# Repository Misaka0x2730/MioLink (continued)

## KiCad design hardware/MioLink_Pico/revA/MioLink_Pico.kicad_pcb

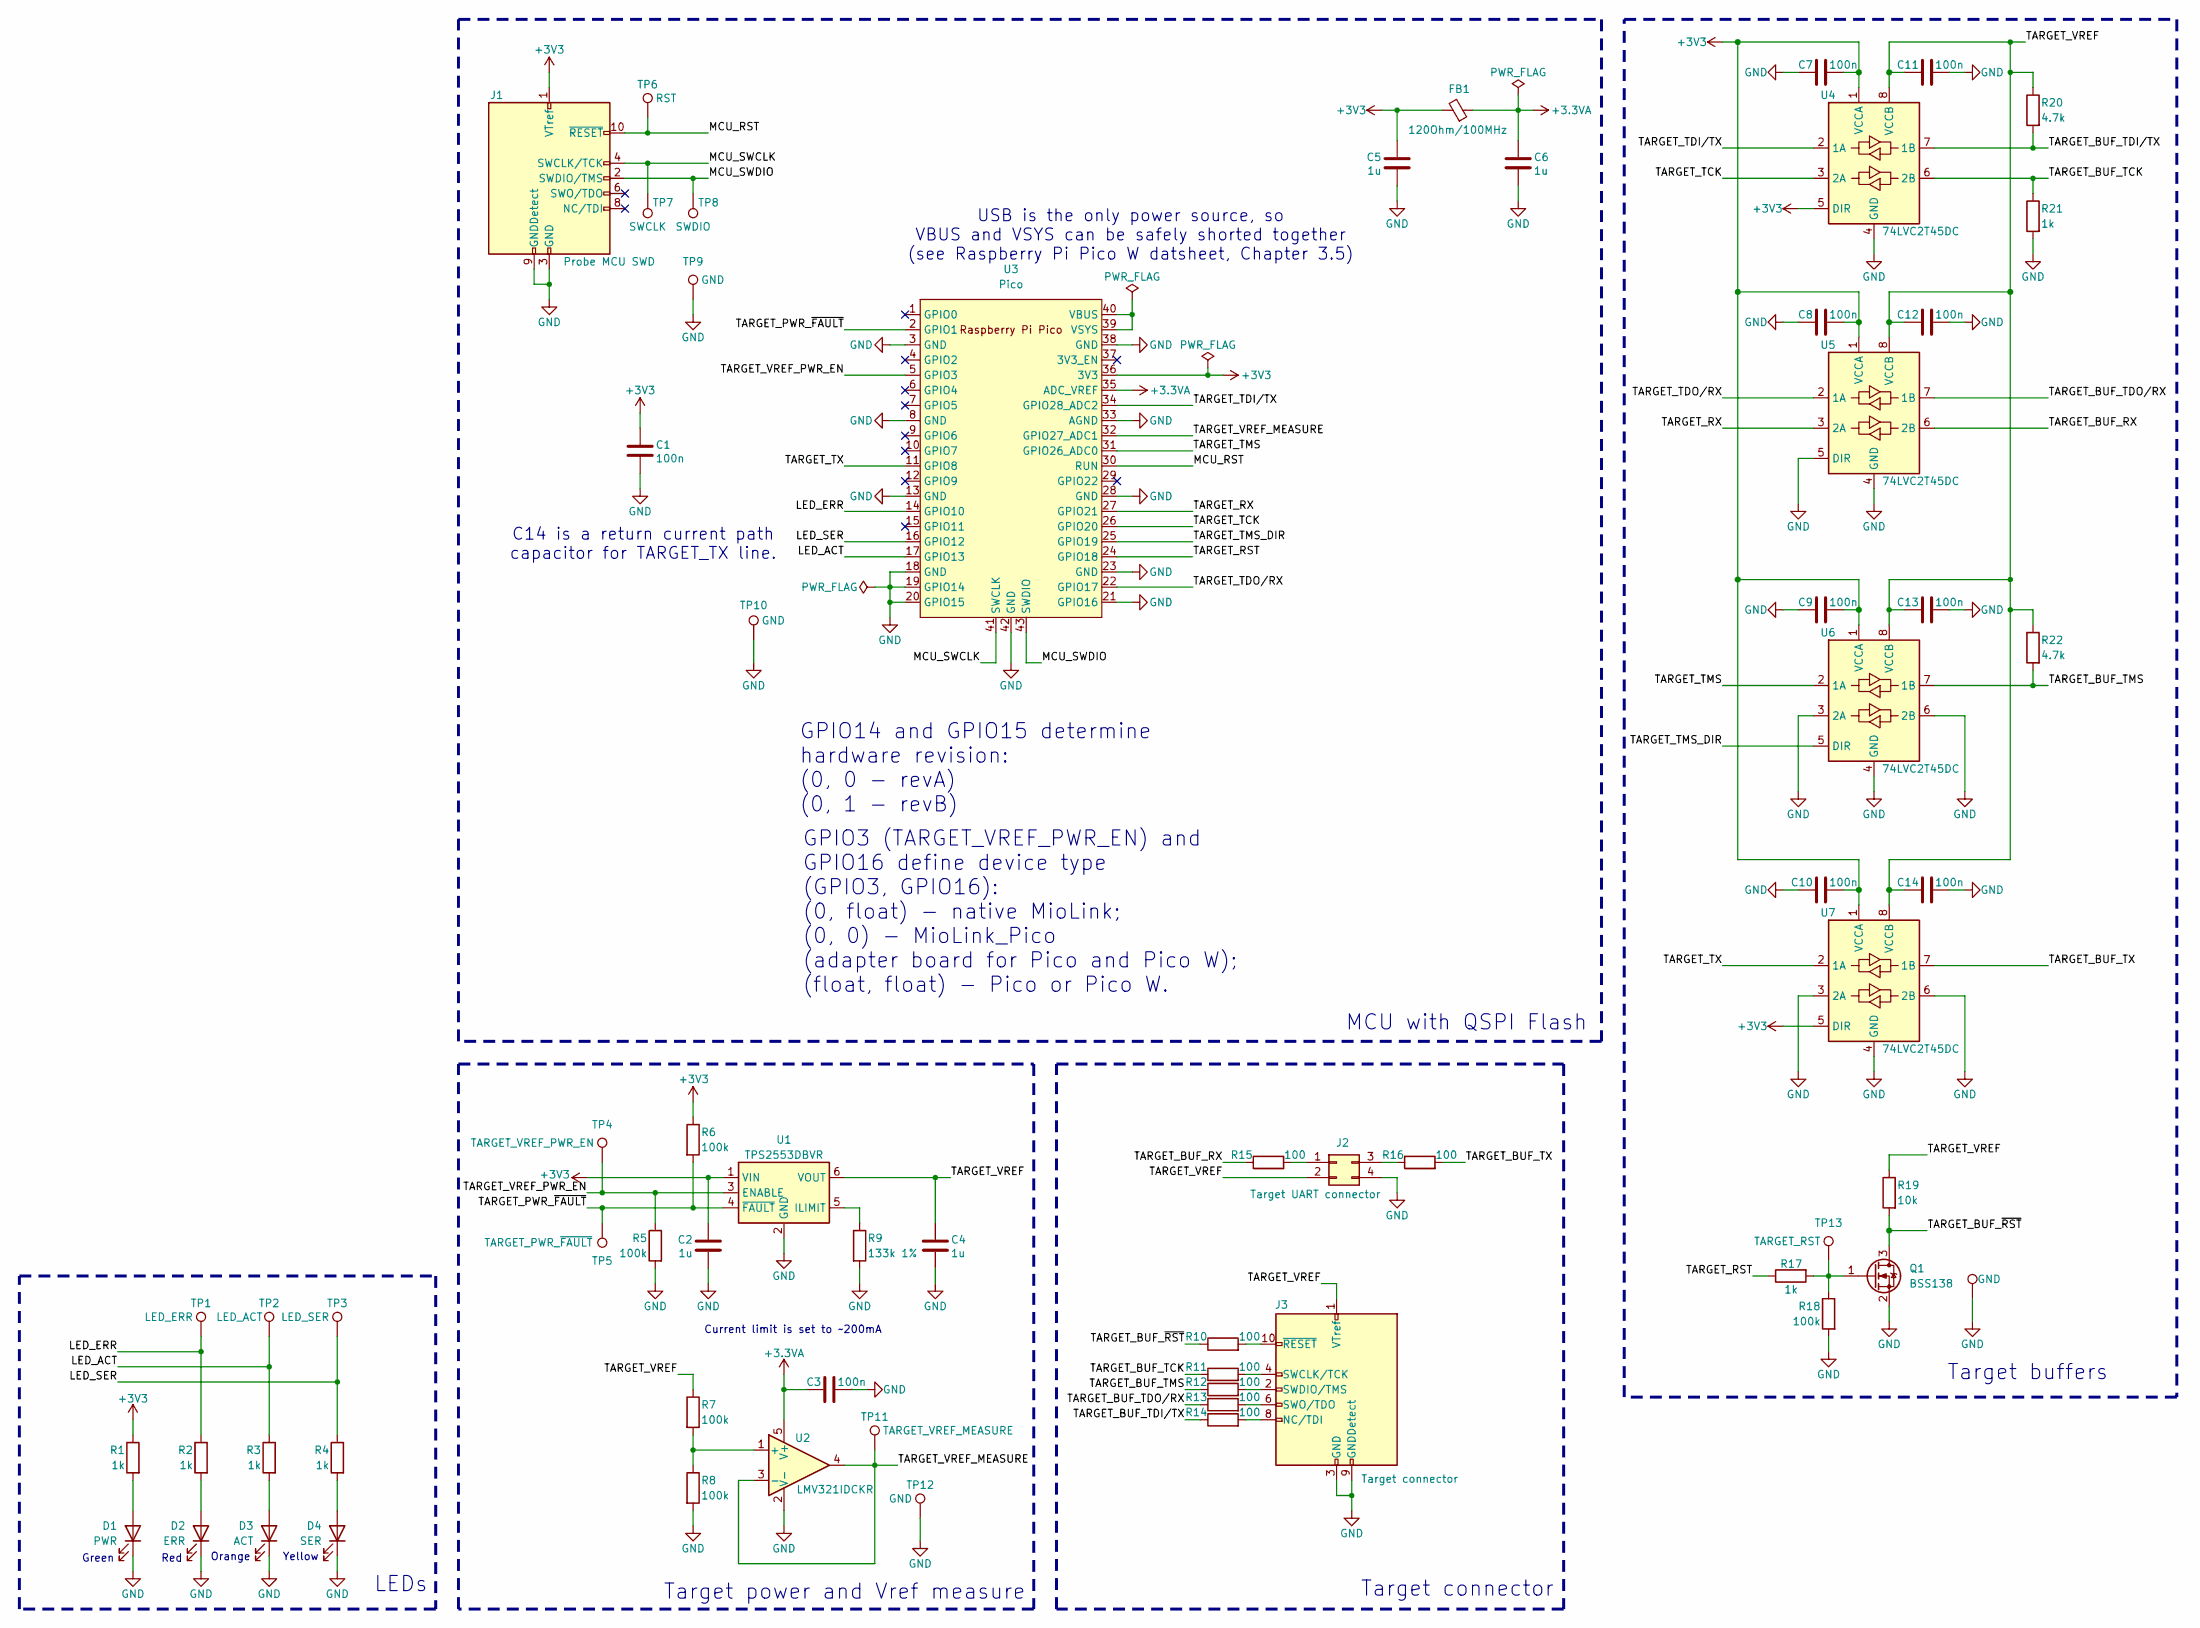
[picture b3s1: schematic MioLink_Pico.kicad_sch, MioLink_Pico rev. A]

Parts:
C1, C3, C7, C8, C9, C10, C11, C12, C13, C14: 100n; C_0402_1005Metric; Part Number CL05B104KO5NNNC; LCSC C1525
C2, C4, C5, C6: 1u; C_0402_1005Metric; Part Number CL05A105KA5NQNC; LCSC C52923
D1: PWR; LED_1206_3216Metric; Part Number XL-3216SYGC; LCSC C965826
D2: ERR; LED_1206_3216Metric; Part Number XL-3216SURC; LCSC C965822
D3: ACT; LED_1206_3216Metric; Part Number XL-3216UOC; LCSC C965823
D4: SER; LED_1206_3216Metric; Part Number XL-3216UYC; LCSC C965824
FB1: 120Ohm/100MHz; L_0603_1608Metric; Part Number BLM18PG121SN1D; LCSC C14709
J1: Probe MCU SWD; PinHeader_2x05_P1.27mm_Vertical_SMD; Part Number 20021121-00010T4LF; LCSC C598540
J2: Target UART connector; PinHeader_2x02_P2.54mm_Horizontal; Part Number PZ254-2-02-W-8.5; LCSC C2894982
J3: Target connector; IDC-Header_2x05_P2.54mm_Horizontal; Part Number 0502A001A1BC; LCSC C7434504
Q1: BSS138; SOT-23; Part Number BSS138LT1G; LCSC C82045
R1, R2, R3, R4, R17, R21: 1k; R_0402_1005Metric; Part Number 0402WGF1001TCE; LCSC C11702
R5, R6, R7, R8, R18: 100k; R_0402_1005Metric; Part Number 0402WGF1003TCE; LCSC C25741
R9: 133k 1%; R_0402_1005Metric; Part Number 0402WGF1333TCE; LCSC C25753
R10, R11, R12, R13, R14, R15, R16: 100; R_0402_1005Metric; Part Number 0402WGF1000TCE; LCSC C25076
R19: 10k; R_0402_1005Metric; Part Number 0402WGF1002TCE; LCSC C25744
R20, R22: 4.7k; R_0402_1005Metric; Part Number 0402WGF4701TCE; LCSC C25900
TP1: LED_ERR; TestPoint_Pad_D1.0mm
TP2: LED_ACT; TestPoint_Pad_D1.0mm
TP3: LED_SER; TestPoint_Pad_D1.0mm
TP4: TARGET_VREF_PWR_EN; TestPoint_Pad_D1.0mm
TP5: TARGET_PWR_~{FAULT}; TestPoint_Pad_D1.0mm
TP6: RST; TestPoint_Pad_D1.0mm
TP7: SWCLK; TestPoint_Pad_D1.0mm
TP8: SWDIO; TestPoint_Pad_D1.0mm
TP9, TP12, TP14: GND; TestPoint_Pad_D1.0mm
TP10: GND; TestPoint_Keystone_5000-5004_Miniature
TP11: TARGET_VREF_MEASURE; TestPoint_Pad_D1.0mm
TP13: TARGET_RST; TestPoint_Pad_D1.0mm
U1: TPS2553DBVR; SOT-23-6; Part Number TPS2553DBV; LCSC C55266
U2: LMV321IDCKR; SOT-353_SC-70-5; Part Number LMV321IDCKR; LCSC C3029047
U3: Pico; RPi_Pico_SMD_TH
U4, U5, U6, U7: 74LVC2T45DC; VSSOP-8_2.3x2mm_P0.5mm; Part Number SN74LVC2T45DCU; LCSC C22356905

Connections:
+3.3VA: C3.1, C6.1, FB1.1, U2.5 (V+), U3.35 (ADC_VREF)
+3V3: C1.2, C2.1, C5.1, C7.1, C8.1, C9.1, C10.1, FB1.2, J1.1 (VTref), R1.1, R6.1, U1.1 (VIN), U3.36 (3V3), U4.1 (VCCA), U4.5 (DIR), U5.1 (VCCA), U6.1 (VCCA), U7.1 (VCCA), U7.5 (DIR)
/LED_ACT: R3.1, TP2.1, U3.17 (GPIO13)
/LED_ERR: R2.1, TP1.1, U3.14 (GPIO10)
/LED_SER: R4.1, TP3.1, U3.16 (GPIO12)
/MCU_RST: J1.10 (~RESET), TP6.1, U3.30 (RUN)
/MCU_SWCLK: J1.4 (SWCLK/TCK), TP7.1, U3.41 (SWCLK)
/MCU_SWDIO: J1.2 (SWDIO/TMS), TP8.1, U3.43 (SWDIO)
/TARGET_BUF_RX: R15.1, U5.6 (2B)
/TARGET_BUF_TCK: R11.1, R21.1, U4.6 (2B)
/TARGET_BUF_TDI/TX: R14.1, R20.2, U4.7 (1B)
/TARGET_BUF_TDO/RX: R13.1, U5.7 (1B)
/TARGET_BUF_TMS: R12.1, R22.2, U6.7 (1B)
/TARGET_BUF_TX: R16.2, U7.7 (1B)
/TARGET_BUF_~RST: Q1.3 (D), R10.1, R19.2
/TARGET_PWR_~FAULT: R6.2, TP5.1, U1.4 (~FAULT), U3.2 (GPIO1)
/TARGET_RST: R17.1, U3.24 (GPIO18)
/TARGET_RX: U3.27 (GPIO21), U5.3 (2A)
/TARGET_TCK: U3.26 (GPIO20), U4.3 (2A)
/TARGET_TDI/TX: U3.34 (GPIO28_ADC2), U4.2 (1A)
/TARGET_TDO/RX: U3.22 (GPIO17), U5.2 (1A)
/TARGET_TMS: U3.31 (GPIO26_ADC0), U6.2 (1A)
/TARGET_TMS_DIR: U3.25 (GPIO19), U6.5 (DIR)
/TARGET_TX: U3.11 (GPIO8), U7.2 (1A)
/TARGET_VREF: C4.1, C11.2, C12.2, C13.2, C14.2, J2.2, J3.1 (VTref), R7.1, R19.1, R20.1, R22.1, U1.6 (VOUT), U4.8 (VCCB), U5.8 (VCCB), U6.8 (VCCB), U7.8 (VCCB)
/TARGET_VREF_MEASURE: TP11.1, U2.3 (-), U2.4, U3.32 (GPIO27_ADC1)
/TARGET_VREF_PWR_EN: R5.1, TP4.1, U1.3 (ENABLE), U3.5 (GPIO3)
GND: C1.1, C2.2, C3.2, C4.2, C5.2, C6.2, C7.2, C8.2, C9.2, C10.2, C11.1, C12.1, C13.1, C14.1, D1.1 (K), D2.1 (K), D3.1 (K), D4.1 (K), J1.3 (GND), J1.5 (GND), J1.9 (GNDDetect), J2.4, J3.3 (GND), J3.5 (GND), J3.9 (GNDDetect), Q1.2 (S), R5.2, R8.2, R9.2, R18.2, R21.2, TP9.1, TP10.1, TP12.1, TP14.1, U1.2 (GND), U2.2 (V-), U3.3 (GND), U3.8 (GND), U3.13 (GND), U3.18 (GND), U3.19 (GPIO14), U3.20 (GPIO15), U3.21 (GPIO16), U3.23 (GND), U3.28 (GND), U3.33 (AGND), U3.38 (GND), U3.42 (GND), U4.4 (GND), U5.4 (GND), U5.5 (DIR), U6.3 (2A), U6.4 (GND), U6.6 (2B), U7.3 (2A), U7.4 (GND), U7.6 (2B)
unnamed: D1.2 (A), R1.2
unnamed: D2.2 (A), R2.2
unnamed: D3.2 (A), R3.2
unnamed: D4.2 (A), R4.2
unnamed: J2.1, R15.2
unnamed: J2.3, R16.1
unnamed: J3.8 (NC/TDI), R14.2
unnamed: J3.4 (SWCLK/TCK), R11.2
unnamed: J3.2 (SWDIO/TMS), R12.2
unnamed: J3.6 (SWO/TDO), R13.2
unnamed: J3.10 (~RESET), R10.2
unnamed: Q1.1 (G), R17.2, R18.1, TP13.1
unnamed: R9.1, U1.5 (ILIMIT)
unnamed: R7.2, R8.1, U2.1 (+)
unnamed: U3.39 (VSYS), U3.40 (VBUS)

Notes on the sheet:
Red
Target buffers
Current limit is set to ~200mA
GPIO3 (TARGET_VREF_PWR_EN) and GPIO16 define device type (GPIO3, GPIO16): (0, float) - native MioLink; (0, 0) - MioLink_Pico (adapter board for Pico and Pico W); (float, float) - Pico or Pico W.
Yellow
MCU with QSPI Flash
Green
GPIO14 and GPIO15 determine hardware revision: (0, 0 - revA) (0, 1 - revB)
Target power and Vref measure
Orange
Target connector
LEDs
C14 is a return current path capacitor for TARGET_TX line.
USB is the only power source, so VBUS and VSYS can be safely shorted together (see Raspberry Pi Pico W datsheet, Chapter 3.5)

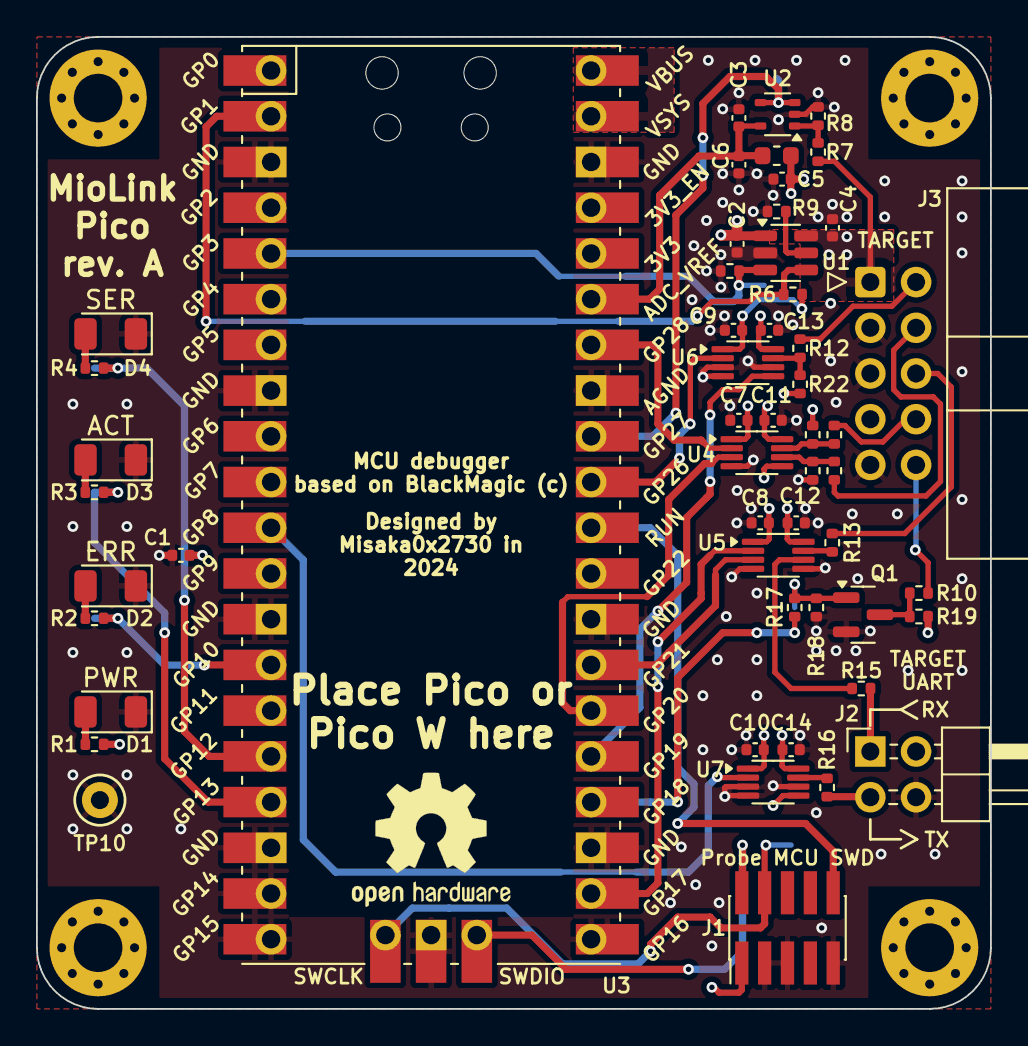
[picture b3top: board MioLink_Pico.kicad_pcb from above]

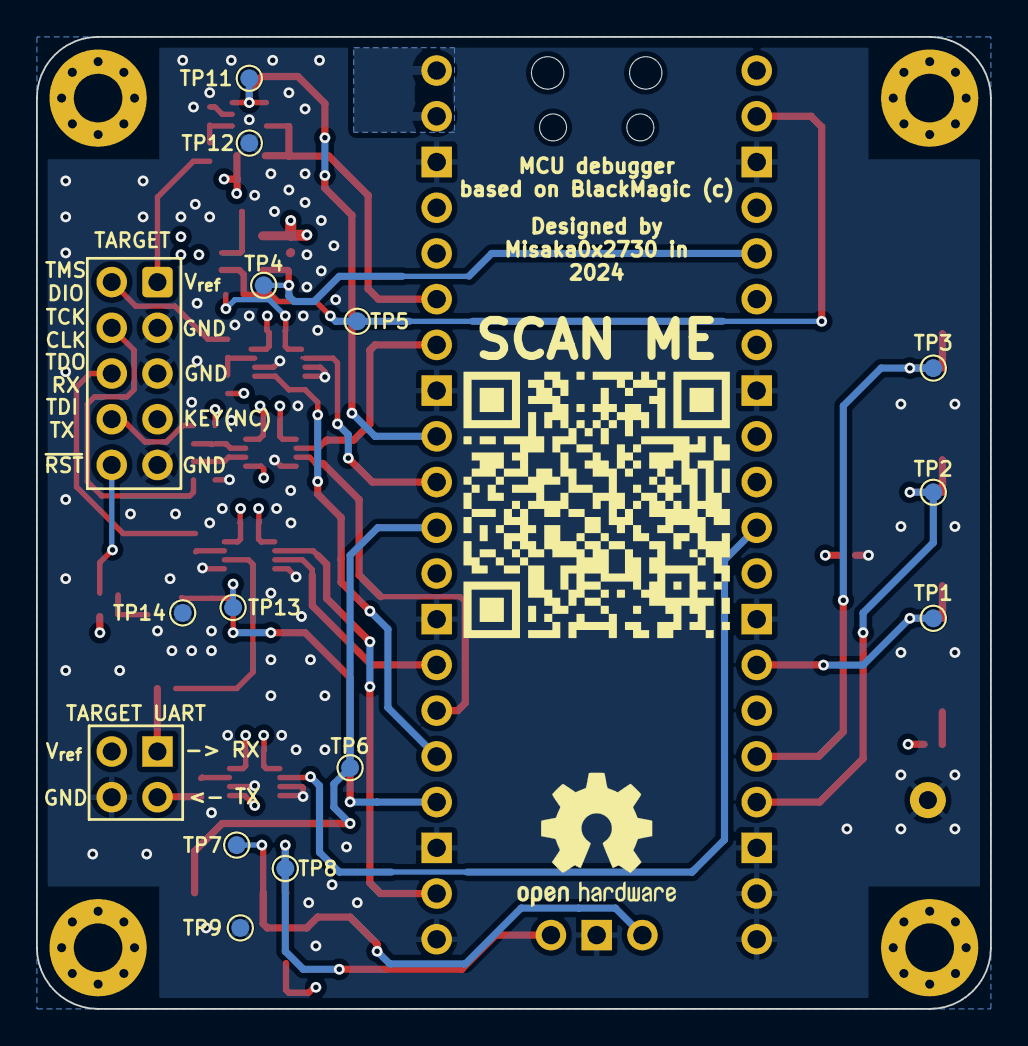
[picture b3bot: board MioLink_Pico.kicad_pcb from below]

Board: 4 copper layers, 53.0 x 54.0 mm, 73 parts (15 on the bottom side), 43 nets.

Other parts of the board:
G1: LOGO
REF1, REF2, REF3, REF4: MountingHole_2.7mm_M2.5_Pad_Via
REF5, REF6: OSHW-Logo2_9.8x8mm_SilkScreen

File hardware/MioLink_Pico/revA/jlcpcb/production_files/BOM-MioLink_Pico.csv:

Comment,Designator,Footprint,LCSC
1k,"R1,R17,R2,R21,R3,R4",R_0402_1005Metric,C11702
120Ohm/100MHz,FB1,L_0603_1608Metric,C14709
100n,"C1,C10,C11,C12,C13,C14,C3,C7,C8,C9",C_0402_1005Metric,C1525
74LVC2T45DC,"U4,U5,U6,U7",VSSOP-8_2.3x2mm_P0.5mm,C22356905
100,"R10,R11,R12,R13,R14,R15,R16",R_0402_1005Metric,C25076
100k,"R18,R5,R6,R7,R8",R_0402_1005Metric,C25741
10k,R19,R_0402_1005Metric,C25744
133k 1%,R9,R_0402_1005Metric,C25753
4.7k,"R20,R22",R_0402_1005Metric,C25900
Target UART connector,J2,PinHeader_2x02_P2.54mm_Horizontal,C2894982
LMV321IDCKR,U2,SOT-353_SC-70-5,C3029047
1u,"C2,C4,C5,C6",C_0402_1005Metric,C52923
TPS2553DBVR,U1,SOT-23-6,C55266
Probe MCU SWD,J1,PinHeader_2x05_P1.27mm_Vertical_SMD,C598540
Target connector,J3,IDC-Header_2x05_P2.54mm_Horizontal,C7434504
BSS138,Q1,SOT-23,C82045
ERR,D2,LED_1206_3216Metric,C965822
ACT,D3,LED_1206_3216Metric,C965823
SER,D4,LED_1206_3216Metric,C965824
PWR,D1,LED_1206_3216Metric,C965826
Pico,U3,RPi_Pico_SMD_TH,
GND,TP10,TestPoint_Keystone_5000-5004_Miniature,
TARGET_VREF_PWR_EN,TP4,TestPoint_Pad_D1.0mm,
SWCLK,TP7,TestPoint_Pad_D1.0mm,
TARGET_PWR_~{FAULT},TP5,TestPoint_Pad_D1.0mm,
GND,TP14,TestPoint_Pad_D1.0mm,
LED_SER,TP3,TestPoint_Pad_D1.0mm,
GND,TP12,TestPoint_Pad_D1.0mm,
TARGET_RST,TP13,TestPoint_Pad_D1.0mm,
GND,TP9,TestPoint_Pad_D1.0mm,
LED_ERR,TP1,TestPoint_Pad_D1.0mm,
LED_ACT,TP2,TestPoint_Pad_D1.0mm,
RST,TP6,TestPoint_Pad_D1.0mm,
TARGET_VREF_MEASURE,TP11,TestPoint_Pad_D1.0mm,
SWDIO,TP8,TestPoint_Pad_D1.0mm,

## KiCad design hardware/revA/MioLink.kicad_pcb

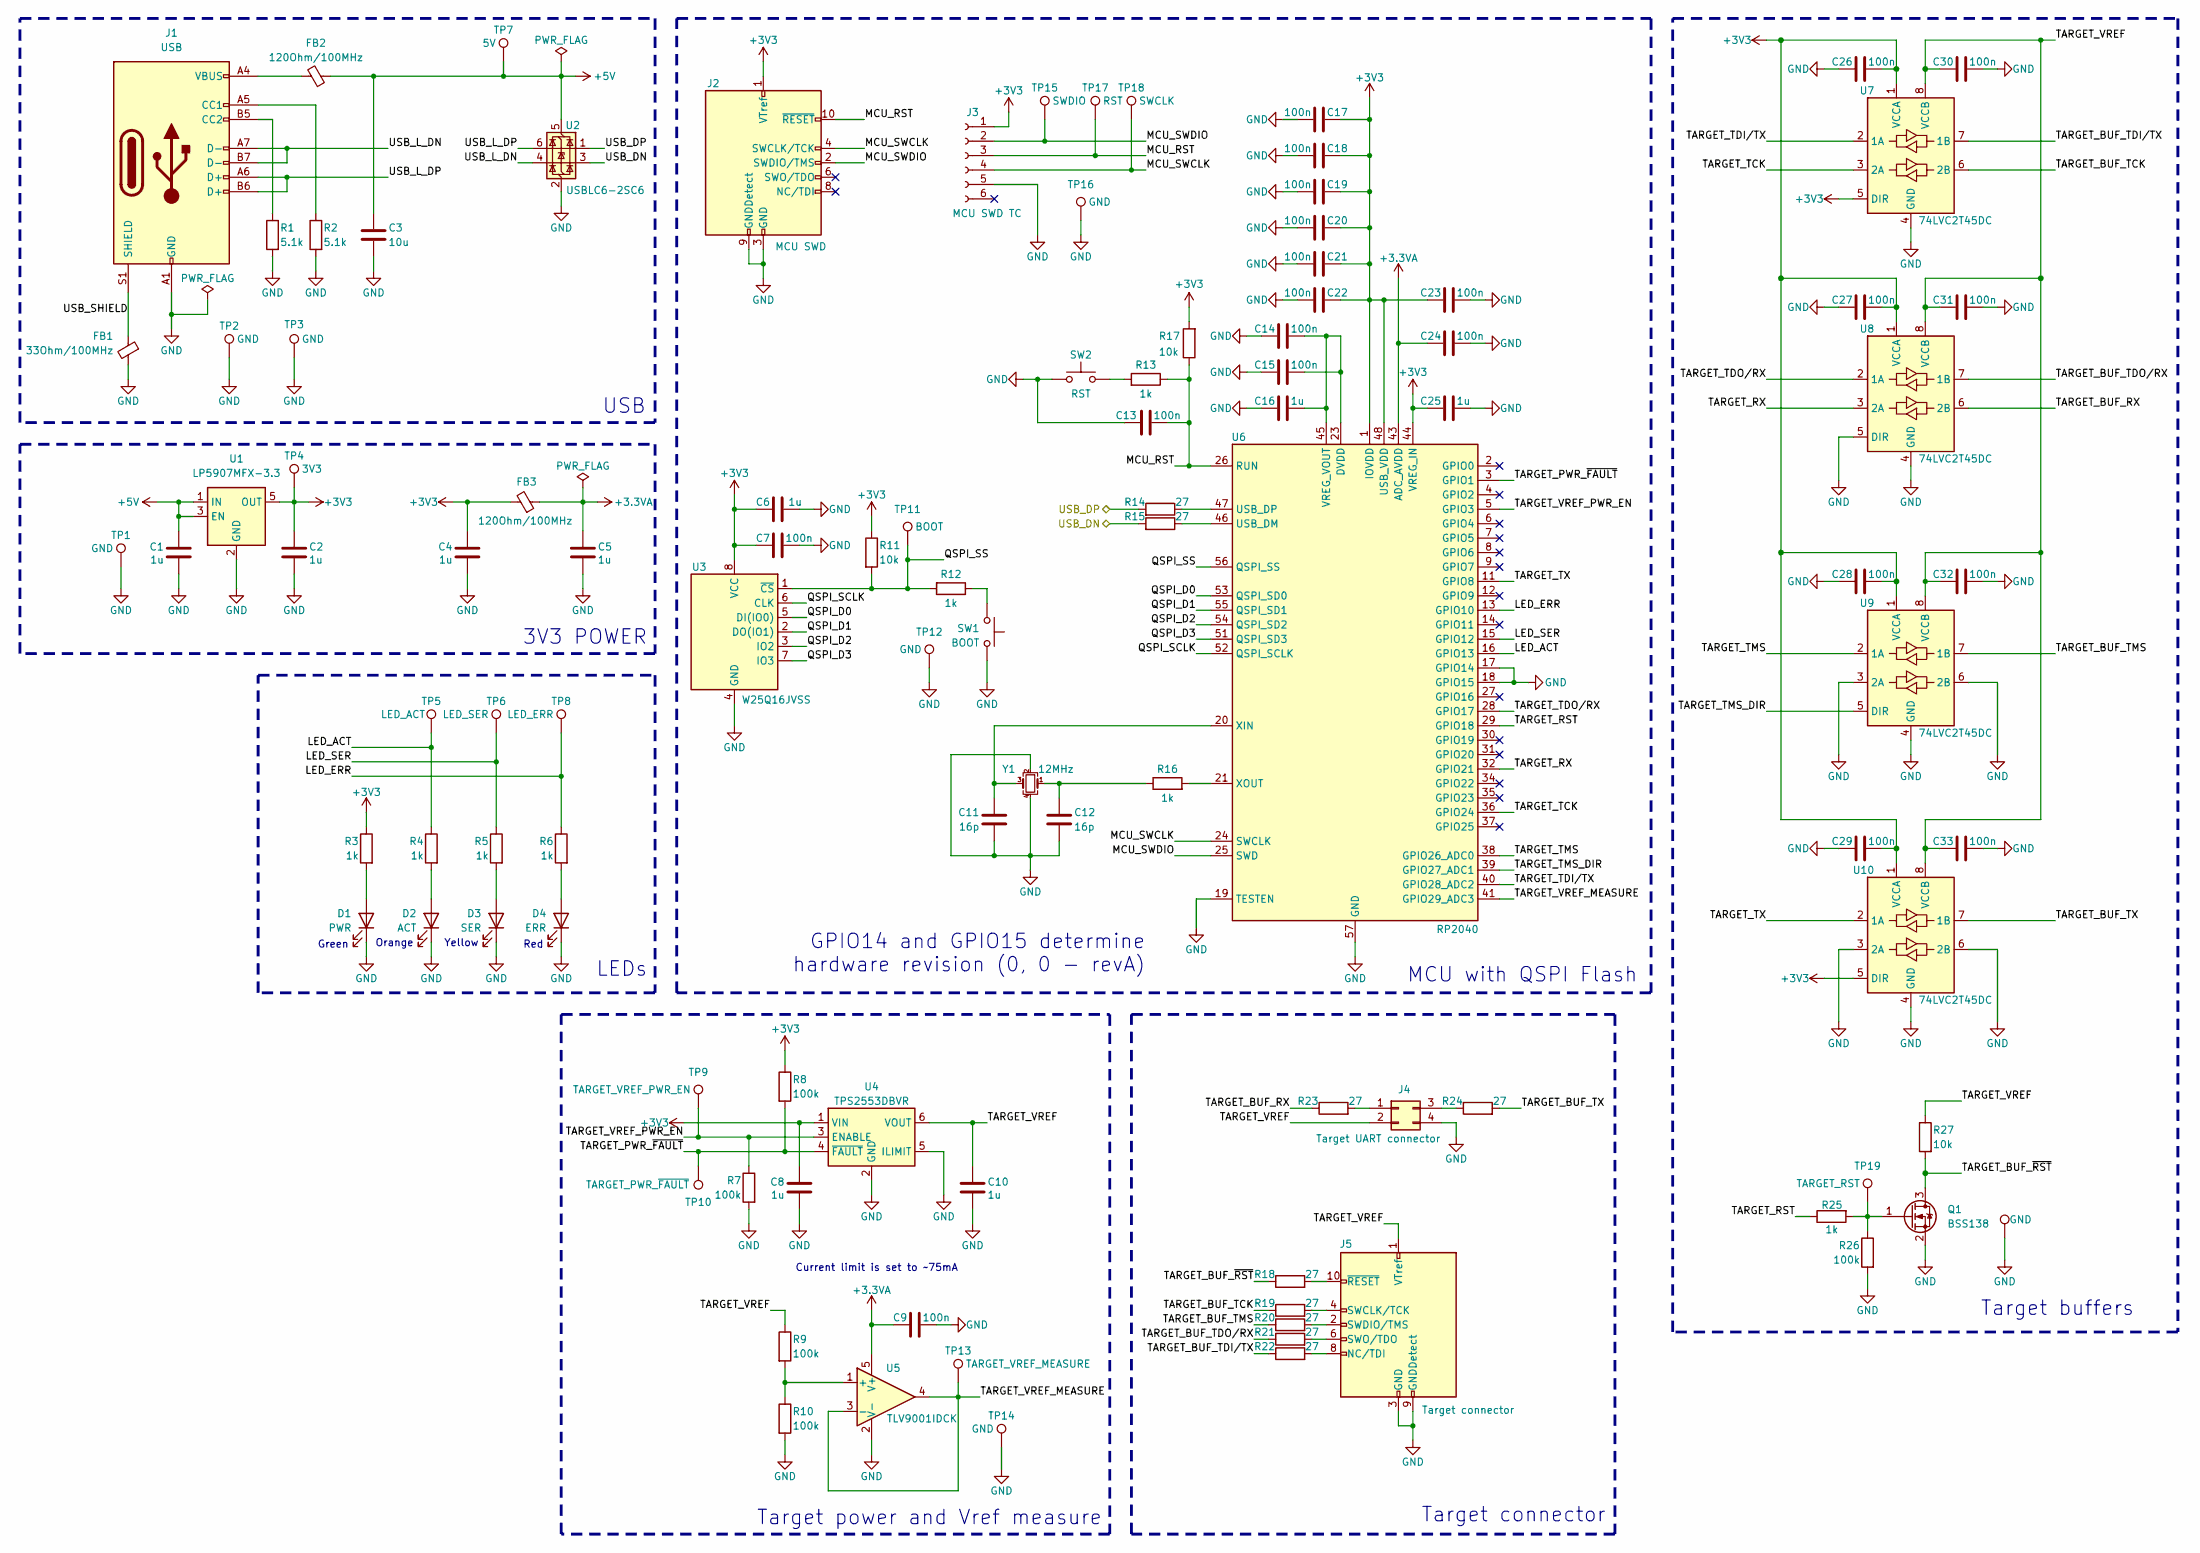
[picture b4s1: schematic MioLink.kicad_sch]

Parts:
C1, C2, C4, C5, C6, C8, C10, C16, C25: 1u; C_0402_1005Metric; Part Number CC0402KRX5R6BB105
C3: 10u; C_0603_1608Metric; Part Number CL10A106KP8NNNC
C7, C9, C13, C14, C15, C17, C18, C19, C20, C21, C22, C23, C24, C26, C27, C28, C29, C30, C31, C32, C33: 100n; C_0402_1005Metric; Part Number CC0402KRX7R7BB104
C11, C12: 16p; C_0402_1005Metric; Part Number CC0402GRNPO9BN160
D1: PWR; LED_1206_3216Metric; Part Number L152L-GC-TR
D2: ACT; LED_1206_3216Metric; Part Number L152L-QOC-TR
D3: SER; LED_1206_3216Metric; Part Number L152L-QYC-TR
D4: ERR; LED_1206_3216Metric; Part Number L150B-QEC-TR
FB1: 33Ohm/100MHz; L_0603_1608Metric; Part Number BLM18PG330SN1D
FB2, FB3: 120Ohm/100MHz; L_0603_1608Metric; Part Number BLM18PG121SN1D
J1: USB; USB_C_Receptacle_HRO_TYPE-C-31-M-12; Part Number TYPE-C-31-M-12A
J2: MCU SWD; PinHeader_2x05_P1.27mm_Vertical_SMD; Part Number M50-3600542R
J3: MCU SWD TC; Tag-Connect_TC2030-IDC-FP_2x03_P1.27mm_Vertical
J4: Target UART connector; PinHeader_2x02_P2.54mm_Horizontal; Part Number M20-9950245
J5: Target connector; IDC-Header_2x05_P2.54mm_Horizontal; Part Number 5103310-1
Q1: BSS138; SOT-23; Part Number BSS138P,215
R1, R2: 5.1k; R_0402_1005Metric; Part Number RC0402FR-075K1L
R3, R4, R5, R6, R12, R13, R16, R25: 1k; R_0402_1005Metric; Part Number RC0402FR-071KL
R7, R8, R9, R10, R26: 100k; R_0402_1005Metric; Part Number RC0402FR-07100KL
R11, R17, R27: 10k; R_0402_1005Metric; Part Number RC0402FR-0710KL
R14, R15, R18, R19, R20, R21, R22, R23, R24: 27; R_0402_1005Metric; Part Number RC0402FR-0727RL
SW1: BOOT; SW_SPST_B3S-1000; Part Number B3S-1000
SW2: RST; SW_SPST_B3S-1000; Part Number B3S-1000
TP1, TP2, TP12, TP14, TP16, TP20: GND; TestPoint_Pad_D1.0mm
TP3: GND; TestPoint_Keystone_5000-5004_Miniature
TP4: 3V3; TestPoint_Pad_D1.0mm
TP5: LED_ACT; TestPoint_Pad_D1.0mm
TP6: LED_SER; TestPoint_Pad_D1.0mm
TP7: 5V; TestPoint_Pad_D1.0mm
TP8: LED_ERR; TestPoint_Pad_D1.0mm
TP9: TARGET_VREF_PWR_EN; TestPoint_Pad_D1.0mm
TP10: TARGET_PWR_~{FAULT}; TestPoint_Pad_D1.0mm
TP11: BOOT; TestPoint_Pad_D1.0mm
TP13: TARGET_VREF_MEASURE; TestPoint_Pad_D1.0mm
TP15: SWDIO; TestPoint_Pad_D1.0mm
TP17: RST; TestPoint_Pad_D1.0mm
TP18: SWCLK; TestPoint_Pad_D1.0mm
TP19: TARGET_RST; TestPoint_Pad_D1.0mm
U1: LP5907MFX-3.3; SOT-23-5; Part Number LP5907MFX-3.3
U2: USBLC6-2SC6; SOT-23-6; Part Number USBLC6-2SC6
U3: W25Q16JVSS; SOIC-8_5.23x5.23mm_P1.27mm; Part Number W25Q16JVSSIQ
U4: TPS2553DBVR; SOT-23-6; Part Number TPS2553DBV
U5: TLV9001IDCK; SOT-353_SC-70-5; Part Number TLV9001IDCK
U6: RP2040; QFN-56-1EP_7x7mm_P0.4mm_EP3.2x3.2mm; Part Number RP2040
U7, U8, U9, U10: 74LVC2T45DC; VSSOP-8_2.3x2mm_P0.5mm; Part Number SN74LVC2T45DCU
Y1: 12MHz; Crystal_SMD_3225-4Pin_3.2x2.5mm; Part Number ABM8-272-T3

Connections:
+3.3VA: C5.1, C9.1, C24.1, FB3.1, U5.5 (V+), U6.43 (ADC_AVDD)
+3V3: C2.1, C4.1, C6.1, C7.1, C8.1, C17.1, C18.1, C19.1, C20.1, C21.1, C22.1, C23.1, C25.1, C26.1, C27.1, C28.1, C29.1, FB3.2, J2.1 (VTref), J3.1, R3.1, R8.1, R11.1, R17.2, TP4.1, U1.5 (OUT), U3.8 (VCC), U4.1 (VIN), U6.1 (IOVDD), U6.10 (IOVDD), U6.22 (IOVDD), U6.33 (IOVDD), U6.42 (IOVDD), U6.44 (VREG_IN), U6.48 (USB_VDD), U6.49 (IOVDD), U7.1 (VCCA), U7.5 (DIR), U8.1 (VCCA), U9.1 (VCCA), U10.1 (VCCA), U10.5 (DIR)
+5V: C1.1, C3.1, FB2.1, TP7.1, U1.1 (IN), U1.3 (EN), U2.5 (VBUS)
/LED_ACT: R4.1, TP5.1, U6.16 (GPIO13)
/LED_ERR: R6.1, TP8.1, U6.13 (GPIO10)
/LED_SER: R5.1, TP6.1, U6.15 (GPIO12)
/MCU_RST: C13.2, J2.10 (~RESET), J3.3, R13.1, R17.1, TP17.1, U6.26 (RUN)
/MCU_SWCLK: J2.4 (SWCLK/TCK), J3.4, TP18.1, U6.24 (SWCLK)
/MCU_SWDIO: J2.2 (SWDIO/TMS), J3.2, TP15.1, U6.25 (SWD)
/QSPI_D0: U3.5 (DI(IO0)), U6.53 (QSPI_SD0)
/QSPI_D1: U3.2 (DO(IO1)), U6.55 (QSPI_SD1)
/QSPI_D2: U3.3 (IO2), U6.54 (QSPI_SD2)
/QSPI_D3: U3.7 (IO3), U6.51 (QSPI_SD3)
/QSPI_SCLK: U3.6 (CLK), U6.52 (QSPI_SCLK)
/QSPI_SS: R11.2, R12.2, TP11.1, U3.1 (~CS), U6.56 (QSPI_SS)
/TARGET_BUF_RX: R23.1, U8.6 (2B)
/TARGET_BUF_TCK: R19.1, U7.6 (2B)
/TARGET_BUF_TDI/TX: R22.1, U7.7 (1B)
/TARGET_BUF_TDO/RX: R21.1, U8.7 (1B)
/TARGET_BUF_TMS: R20.1, U9.7 (1B)
/TARGET_BUF_TX: R24.2, U10.7 (1B)
/TARGET_BUF_~RST: Q1.3 (D), R18.1, R27.2
/TARGET_PWR_~FAULT: R8.2, TP10.1, U4.4 (~FAULT), U6.3 (GPIO1)
/TARGET_RST: R25.1, U6.29 (GPIO18)
/TARGET_RX: U6.32 (GPIO21), U8.3 (2A)
/TARGET_TCK: U6.36 (GPIO24), U7.3 (2A)
/TARGET_TDI/TX: U6.40 (GPIO28_ADC2), U7.2 (1A)
/TARGET_TDO/RX: U6.28 (GPIO17), U8.2 (1A)
/TARGET_TMS: U6.38 (GPIO26_ADC0), U9.2 (1A)
/TARGET_TMS_DIR: U6.39 (GPIO27_ADC1), U9.5 (DIR)
/TARGET_TX: U6.11 (GPIO8), U10.2 (1A)
/TARGET_VREF: C10.1, C30.2, C31.2, C32.2, C33.2, J4.2, J5.1 (VTref), R9.1, R27.1, U4.6 (VOUT), U7.8 (VCCB), U8.8 (VCCB), U9.8 (VCCB), U10.8 (VCCB)
/TARGET_VREF_MEASURE: TP13.1, U5.3 (-), U5.4, U6.41 (GPIO29_ADC3)
/TARGET_VREF_PWR_EN: R7.1, TP9.1, U4.3 (ENABLE), U6.5 (GPIO3)
/USB_DN: R15.2, U2.3 (I/O2)
/USB_DP: R14.2, U2.1 (I/O1)
/USB_L_DN: J1.A7 (D-), J1.B7 (D-), U2.4 (I/O2)
/USB_L_DP: J1.A6 (D+), J1.B6 (D+), U2.6 (I/O1)
/USB_SHIELD: FB1.1, J1.S1 (SHIELD)
GND: C1.2, C2.2, C3.2, C4.2, C5.2, C6.2, C7.2, C8.2, C9.2, C10.2, C11.2, C12.2, C13.1, C14.1, C15.1, C16.1, C17.2, C18.2, C19.2, C20.2, C21.2, C22.2, C23.2, C24.2, C25.2, C26.2, C27.2, C28.2, C29.2, C30.1, C31.1, C32.1, C33.1, D1.1 (K), D2.1 (K), D3.1 (K), D4.1 (K), FB1.2, J1.A1 (GND), J1.A12 (GND), J1.B1 (GND), J1.B12 (GND), J2.3 (GND), J2.5 (GND), J2.9 (GNDDetect), J3.5, J4.4, J5.3 (GND), J5.5 (GND), J5.9 (GNDDetect), Q1.2 (S), R1.2, R2.2, R7.2, R10.2, R26.2, SW1.1, SW2.1, TP1.1, TP2.1, TP3.1, TP12.1, TP14.1, TP16.1, TP20.1, U1.2 (GND), U2.2 (GND), U3.4 (GND), U4.2 (GND), U4.5 (ILIMIT), U5.2 (V-), U6.17 (GPIO14), U6.18 (GPIO15), U6.19 (TESTEN), U6.57 (GND), U7.4 (GND), U8.4 (GND), U8.5 (DIR), U9.3 (2A), U9.4 (GND), U9.6 (2B), U10.3 (2A), U10.4 (GND), U10.6 (2B), Y1.2, Y1.4
unnamed: C12.1, R16.1, Y1.1
unnamed: D1.2 (A), R3.2
unnamed: D2.2 (A), R4.2
unnamed: D3.2 (A), R5.2
unnamed: D4.2 (A), R6.2
unnamed: FB2.2, J1.A4 (VBUS), J1.A9 (VBUS), J1.B4 (VBUS), J1.B9 (VBUS)
unnamed: J1.A5 (CC1), R2.1
unnamed: J1.B5 (CC2), R1.1
unnamed: J4.1, R23.2
unnamed: J4.3, R24.1
unnamed: J5.8 (NC/TDI), R22.2
unnamed: J5.4 (SWCLK/TCK), R19.2
unnamed: J5.2 (SWDIO/TMS), R20.2
unnamed: J5.6 (SWO/TDO), R21.2
unnamed: J5.10 (~RESET), R18.2
unnamed: Q1.1 (G), R25.2, R26.1, TP19.1
unnamed: R12.1, SW1.2
unnamed: R13.2, SW2.2
unnamed: R9.2, R10.1, U5.1 (+)
unnamed: R15.1, U6.46 (USB_DM)
unnamed: R14.1, U6.47 (USB_DP)
unnamed: C14.2, C15.2, C16.2, U6.23 (DVDD), U6.45 (VREG_VOUT), U6.50 (DVDD)
unnamed: C11.1, U6.20 (XIN), Y1.3
unnamed: R16.2, U6.21 (XOUT)

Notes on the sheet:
Red
Target buffers
Current limit is set to ~75mA
Yellow
MCU with QSPI Flash
Green
GPIO14 and GPIO15 determine hardware revision (0, 0 - revA)
Target power and Vref measure
Orange
Target connector
LEDs
USB
3V3 POWER

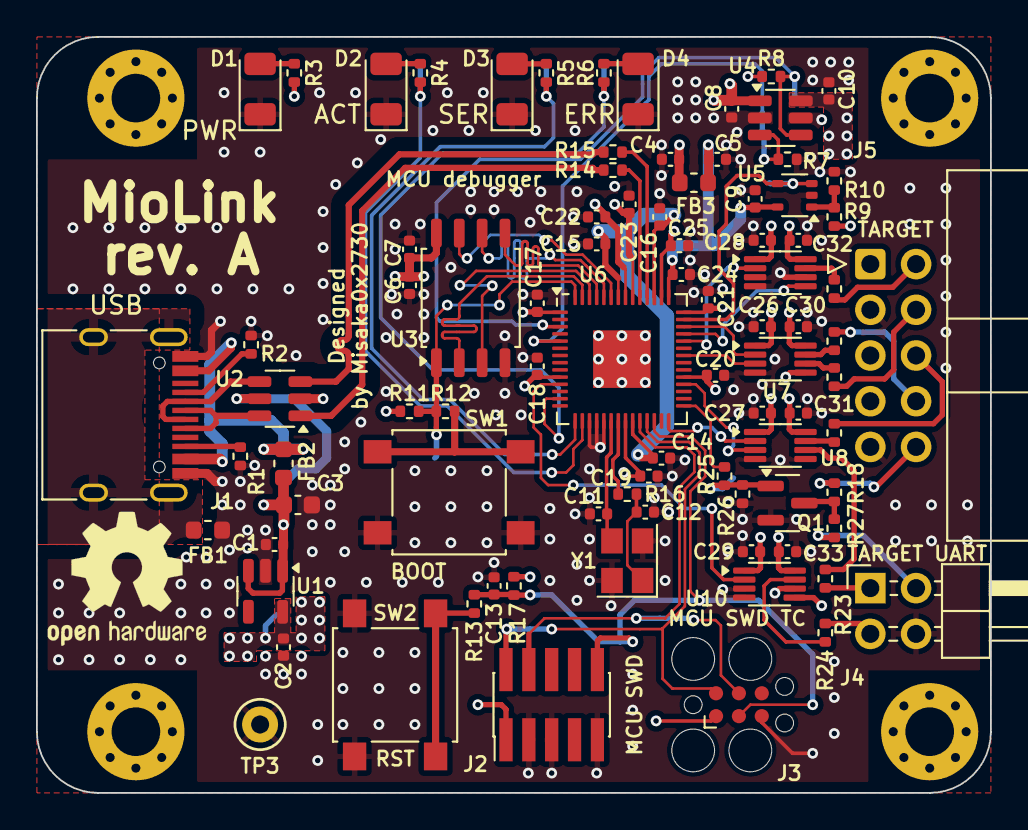
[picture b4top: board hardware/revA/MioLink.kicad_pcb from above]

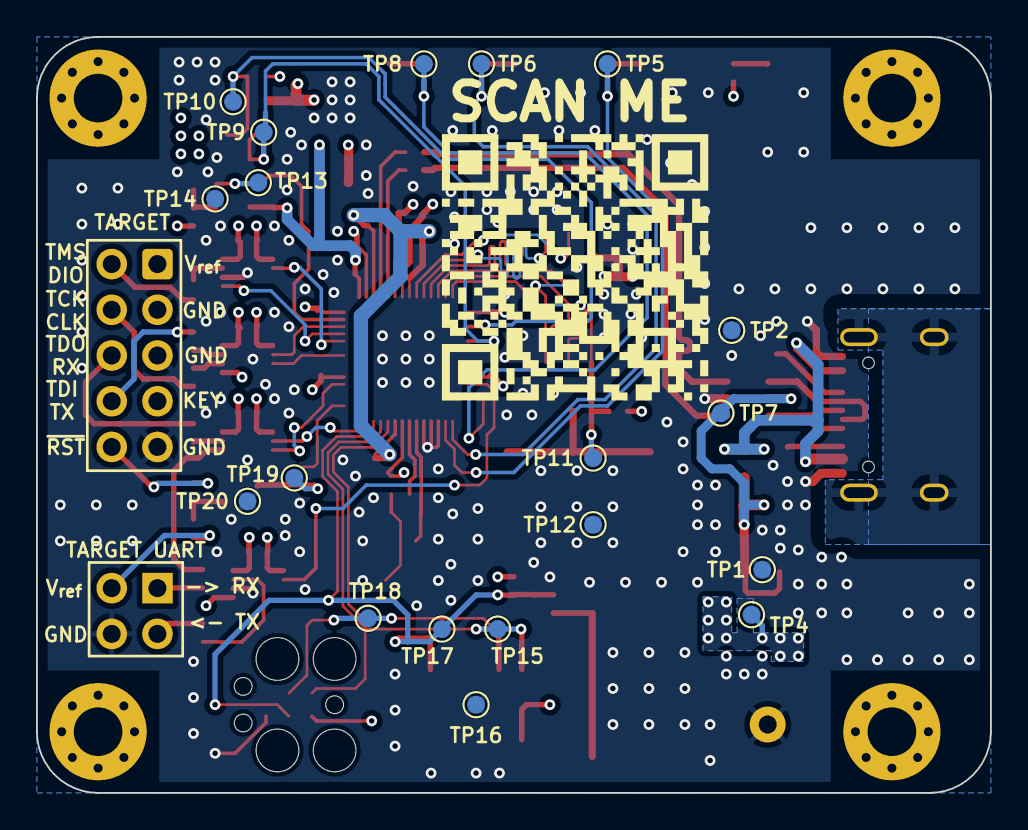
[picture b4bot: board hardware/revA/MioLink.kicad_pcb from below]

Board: 4 copper layers, 53.0 x 42.0 mm, 108 parts (20 on the bottom side), 64 nets.

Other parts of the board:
G1: LOGO
REF5: OSHW-Logo2_9.8x8mm_SilkScreen

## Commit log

2024-06-16 Added blackmagic as submodule
2024-06-19 revA hardware (SCH+PCB) finished development
2024-06-19 Updated part numbers
2024-07-16 Finished revA, added JLCPCB production files
2024-07-28 Updated submodules, added FreeRTOS-Kernel
2024-07-30 Initial firmware commit, implemented platform support for RubyLink (test platform, MioLink is still in production)
2024-08-04 Added PIOSM SWD implementation, added crc32 implementation on RP2040 DMA
2024-08-04 Use RP2040 crc32 implementation in CMakeLists, use registers instead of SDK calls in swdptap_seq_out_parity, fixed target interface frequency calcualtion (removed flaot)
2024-08-04 Used task notification for GDB RX data. Added PIOSM implementation for adiv5_swd_raw_access and adiv5_swd_write_no_check
2024-08-05 Added detailed description for target_swd.pio program, refactor swdtap.c
2024-08-07 Optimized SWD PIO code, now there is no need to send to TX FIFO dummy data when number of cycles is 32 (autopull threshold). Include RTT files and init RTT onlu wjem debug is enabled (ENABLE_DEBUG=1)
2024-08-07 Added JTAG PIO implementation
2024-08-07 GDB (gdb_if) USB code optimization
2024-08-08 Revork JTAG PIO implementation
2024-08-09 JTAG PIO program rework. Added common functions to work with PIO in tap_pio_common.h
2024-08-09 Minor PIO jtag/swd fixes
2024-08-12 Fix usb serial code
2024-08-14 Removed RubyLink platform. Rework USB-UART module.
2024-08-15 Added automatic git version generating for BMP and FreeRTOS. Added RTT driver (rtt_if).
2024-08-17 Updated submodules
2024-08-17 Minor code refactoring, decreased gdb_if buffers from 1024 to 512
2024-08-17 Added TRACESWO support (UART only), added TRACE and DFU interfaces in USB descriptors
2024-08-17 Added support for the UART on TDI/TDO pins feature (command "monitor uart_on_tdi_tdo")
2024-08-18 Reduced FreeRTOS heap size
2024-08-18 Minor refactoring, implemented rtos_heapinfo and cmd_rtos_tasksinfo platform commands
2024-08-19 Use GCC printf instead of Pico SDK implementation
2024-08-19 Minor refactoring of platform commands
2024-08-19 Rework of send_to_usb function
2024-08-19 Added _write sycall implementation for ENABLE_DEBUG=1
2024-08-19 Refactoring CMakeLists, removed unused aux_serial.h, added USE_SYSVIEW_TRACE to enable\disable SystemView tracing
2024-08-19 Removed unnecerssary "if CMAKE_COMPILER_IS_GNUCC" in CMakeLists
2024-08-19 CMakeLists rework
2024-08-19 Added rev.A and rev.B definitions in platform.h
2024-08-19 Removed hack for using tinyusb FreeRTOS support instead of Pico SDK. Reworked send_to_usb function
2024-08-19 Added version generating for MioLink by using git tags
2024-08-19 Added missed header tusb_config.h
2024-08-23 Added Microsoft OS 2.0 Descriptor
2024-08-23 Fixed comment for Microsoft OS 2.0 descriptor
2024-08-29 Major usb_serial, traceswo refactoring
2024-09-21 Global project rework, added hardware project files: MioLink revB, MioLink adapter revA, MioLink Pico revA (main board for Pico and Pico W)
2024-09-23 Fixed problems with release build
2024-09-23 Updated FreeRTOS-Kernel
2024-09-23 Added schematics in .pdf
2024-10-03 Fixed a lot of minor issues, added Pico and Pico W support
2024-10-03 Run .clang-format over all MioLink files
2024-10-04 Updated copyright, delay in pio programs, schematic pdf's
2024-10-08 Global code cleanup, fixed a lot of minor moments. Added description to SWD/JTAG PIO programs
2024-10-11 Rework SWD PIO programs, split programs and use all state machines
2024-10-11 Enabled multicore execution
2024-10-11 Disabled multi-core for testing
2024-10-26 Removed README to docs folder
2024-10-26 Moved _config.yml to docs
2024-10-27 Fixed relative paths in CMakeLists.txt, updated submodules
2024-10-27 Update custom page
2024-10-28 Added Gemfile
2024-10-28 Updated _includes/header.html
2024-10-28 Pre-release workflow cleanup, added release workflow
2024-11-02 Fixed compiler errors after blackmagic sync
2024-11-02 Reworked SWD code (DMA is used to send data to the PIO TX FIFO), minor changes, moved GDB thread to Core 1
2024-11-02 Code reformat
2024-11-02 Minor swdtap refactoring
2024-11-02 Added SWDP_ACK_OK define in bmp/swdtap.c
2024-11-02 Rework JTAG code, use DMA to send data to PIO TX FIFO
2024-11-02 Fixed comments in target_jtag.pio
2024-11-02 Removed unused code
2024-11-03 Removed unnecessary delays in target_jtag.pio
2024-11-10 Implemented new JTAG PIO program
2024-11-24 Fixed the HW version pins numbers
2024-11-24 Added comments for the target_jtag program
2024-11-24 Fixed .obj extensions in the linker scripts
2024-11-25 Minor refactoring, removed unnecessary newlines
2024-11-26 Fixed comment in target_jtag
2024-11-26 Clear PIO FIFOs after JTAG and SWD sub-programs
2025-01-02 Updated third-party libraries
2025-02-10 Minor refactoring
2025-02-10 Update submodules
2025-02-14 Update FreeRTOS-Kernel
2025-02-14 Add TRACESWO Manchester mode support
2025-02-14 Added .DS_Store to .gitignore
2025-02-27 Update .gitignore to ignore picotool and test board files
2025-02-27 Add FIFO join configuration for SWO initialization
2025-02-27 Update TRACESWO Manchester mode to use 12 cycles per bit
2025-02-27 Refactor header guards and include order in multiple files;
2025-10-04 Updated third-party libraries, resolved conflicts
2025-10-04 Changed blackmagic branch to pass-baudrate-in-manchester-mode
2025-10-04 Fixed Dmitry Rezvanov email in headers
2025-10-04 gdb_if refactoring
2025-10-04 Minor refactoring, created platform_swdtap.h header for swdtap_adiv5 functions
2025-10-04 Fixed debug PLATFORM_IDENT
2025-10-04 Refactor includes across multiple source files for consistency and organization
2025-10-04 Minor refactoring USB serial and traceswo
2025-10-04 Renamed timing_rp2040 to platform_timing
2025-10-04 Renamed USB_CDC_NOTIF_UART_x to SB_CDC_NOTIF_SERIAL_x
2025-10-04 Moved pio programs to pio folder
2025-10-04 Renamed platform_get_max_interface_freq to platform_get_interface_periph_clk
2025-10-05 Removed hardware includes from platform.h
2025-10-05 Removed USB_CDC_NOTIF_SERIAL_RX_FLUSH notification
2025-10-06 Fixed IDENT defines
2025-10-06 Fixed bug with incorrect SWD frequency
2025-10-06 Fixed PIO gpio configuration
2025-10-06 Updated blackmagic branch to miolink_fixes
2025-11-12 Update third-party submodules
2025-11-12 Update README.md
    Removed known issues section
2026-05-10 Code refactoring
2026-05-11 Added instructions for Claude, added file templates
2026-05-11 usb_serial and traceswoasync refactoring
2026-05-13 Added uart_bridge initialization, fixed verification issue on STM32F1
2026-05-15 Comprehensive code refactoring
2026-05-16 Fixed wrong platform when auto-detect is enabled
2026-05-16 Minor uart_bridge refactoring
2026-05-16 Use maximum MCU frequency
2026-05-16 Updated PICO_BOARD info in README
2026-05-16 Ignore Cursor logs
2026-05-17 Improved auto-detect
2026-05-17 Implemented RP2350 support
2026-05-17 Added mention of RP2350 support in README
2026-05-18 Added some popular boards to CI/CD build, renamed auto build to auto_rp2040
2026-05-18 Minor CI/CD config refactoring
2026-05-18 Allow build-main manual run
2026-05-18 Minor build-main.yml refactoring
2026-05-18 Added explanation for intentional drain (level - 1) bytes from UART RX FIFO
2026-05-18 Use UART_BRIDGE_RX_BUFFER_ADVANCE also for buffers in INT mode
2026-05-18 uart_bridge refactoring - check number of buffers, calculate the wrap value in runtime, added enum's for FIFO levels
2026-05-18 Added additional check for timer_period to avoid division by zero in uart_bridge_configure_uart
2026-05-18 Clear RX buffers in uart_bridge_configure_uart
2026-05-18 Fixed minor codestyle moments
2026-05-18 CMakeLists refactoring, removed BOARD_SELECTOR
2026-05-18 Rearranged headers
2026-05-18 Fixed compiler error in platform_board.h (use autogen board config)
2026-05-18 Updated blackmagic and tinyusb submodules
2026-05-18 Fixed missing PICO_VSYS_PIN in the auto_rp2040 build
2026-05-18 Added MioLink and MioLink_Pico platforms to the CI/CD build
2026-05-19 Fixed cod style violations, minor problems
2026-05-19 Code refactoring, refactoring USB descriptors
2026-05-19 Minor code refactoring
2026-05-22 Added delay between adc_read in the platform detect
2026-05-22 Fixed tinyusb and pico-sdk import order to avoid selecting tinyusb from pico-sdk
2026-05-22 Updated comment for PICO_W_DETECT_ADC_THRESHOLD
2026-05-24 Implemented thread-safe version of morse.c
2026-05-24 Updated blackmagic submodule
2026-05-24 Use target_serial_get_dtr in traceswodecode
2026-05-24 Refactoring USB string descriptor length calculations
2026-05-24 Release TDI/TDO UART before JTAG initialization
2026-05-24 Check min_freq in tap_pio_set_sm_freq before calculations
2026-05-25 Disable configSUPPORT_PICO_SYNC_INTEROP and configSUPPORT_PICO_TIME_INTEROP for single-core mode
2026-05-25 Fixed issue with a lot of zeros after opening serial port
2026-05-25 Comments refactoring
2026-05-25 Fixed swdptap_seq_in_parity when clock_cycles < TAP_PIO_MAX_TICKS_PER_TRANSFER
2026-05-26 Limit tpwr_consecutive_faults to TPWR_FAULT_STREAK_LIMIT
2026-05-26 Disable MIOLINK_TYPE_PIN_0 pulls after the type detection
2026-05-26 Rework platform_max_frequency_get, calculate the frequency from PIO divider register value
2026-05-26 Fixed potential race condition in swo_init
2026-05-26 GDB: subscribe task to USB_CDC_NOTIF_LINE_STATE_UPDATE, add vTaskDelay for the case when host is disconnected
2026-05-26 Disable DMA sniffer after calculating CRC32
2026-05-26 Recover PIO SM in the case of TAP PIO timeout
2026-05-26 Use 2 stop bits if 1.5 was selected
2026-05-26 Fixed uart_bridge_rx_dma_finish_receiving, disable interrupt for rx channel and wait until ISR on another core is finished
2026-05-26 Fixed DFU descriptor
2026-05-28 Updated linker scripts, for RP2350 release build - copy firmware to RAM
2026-05-30 Added dispatch-tests
2026-05-31 Added manual trigger to dispatch-tests
2026-06-06 Added .claude folder to gitignore
2026-06-06 Updated CI config - rename to Firmware CI, run tests only by manual trigger
2026-06-06 Renamed the test bench project to MioLink_TestBench
2026-06-06 Renamed CI config
